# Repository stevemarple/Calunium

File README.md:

# Calunium

Calunium is an Arduino clone using the ATmega164A, ATmega164PA
ATmega324A, ATmega324PA, ATmega644A, ATmega644PA, ATmega1284 or
ATmega1284P microcontroller. The layout is designed for easy assembly
and maximum compatibility with the Arduino Uno, with additional
functionality being compatible with the Arduino Mega(2560).

## License

Unless indicated otherwise hardware is released under the Creative
Commons Attribution-ShareAlike 3.0 Unported (CC BY-SA 3.0)
http://creativecommons.org/licenses/by-sa/3.0/

Unless indicated otherwise software is released under the GNU Lesser
General Public License, version 2.1.
http://www.gnu.org/licenses/lgpl-2.1.html

## Versions

A brief description of the versions is given below. In each case
peripherals can be omitted form the build if not need.

### Stripboard version

The analogue pin mapping differs slightly for the stripboard
version. For more information see
http://blog.stevemarple.co.uk/2011/08/introducing-calunium-arduino-clone.html

### PCB version 1

Includes a real-time clock and LM61 temperature sensor. Standard
Arduino headers and JTAG, FTDI and auxillary power connectors. USB
connector for power and V-USB interface (not confirmed to work). Can
be operated at 3.3V or 5V depending upon build configuration. Not
jumper selectable. For more information see
http://blog.stevemarple.co.uk/2011/11/calunium-pcb-version.html.

### PCB version 2

Includes real-time clock, micro-SD socket, RFM12B radio module, and
LM61 temperature sensor. Arduino 1.0 headers with IOREF and dedicated
I2C pins. JTAG, FTDI and auxillary power connectors.  USB connector
for power only. Jumper-selectable 3.3V or 5V operation. For more
information see
http://blog.stevemarple.co.uk/2012/12/calunium-version-2.html

### PCB version 2.1

Includes MCP2200 USB-UART converter, real-time clock, micro-SD socket,
RFM12B radio module, and LM61 temperature sensor. Arduino 1.0 headers
with IOREF and dedicated I2C pins. JTAG and auxillary power
connectors. If the MCP2200 is fitted then the FTDI connector cannot be
fitted, but the USB socket is enabled for data. If the MCP2200 is not
fitted the FTDI connector can be, but the USB socket is for power
only. Jumper-selectable 3.3V or 5V operation. For more information see

The headers include
IOREF and dedicated I2C pins. For more information see
http://blog.stevemarple.co.uk/2013/02/calunium-version-21.html and
http://blog.stevemarple.co.uk/2012/12/calunium-version-2.html.

## Bootloader

Xboot and OptiBoot bootloaders are included. To avoid too many items
in boards menu the optiboot versions are commented out.

The xboot source files can be found at
https://github.com/stevemarple/xboot.

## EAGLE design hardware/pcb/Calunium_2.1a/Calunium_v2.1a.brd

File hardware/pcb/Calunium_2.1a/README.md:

# Calunium v2.1a PCB design

Calunium design files for Eagle 6.2.0.

Identical to Calunium v2.1 but corrects for silkscreen error on JP9.

## Licence
Creative Commons Attribution-ShareAlike 3.0 Unported (CC BY-SA 3.0)
http://creativecommons.org/licenses/by-sa/3.0/

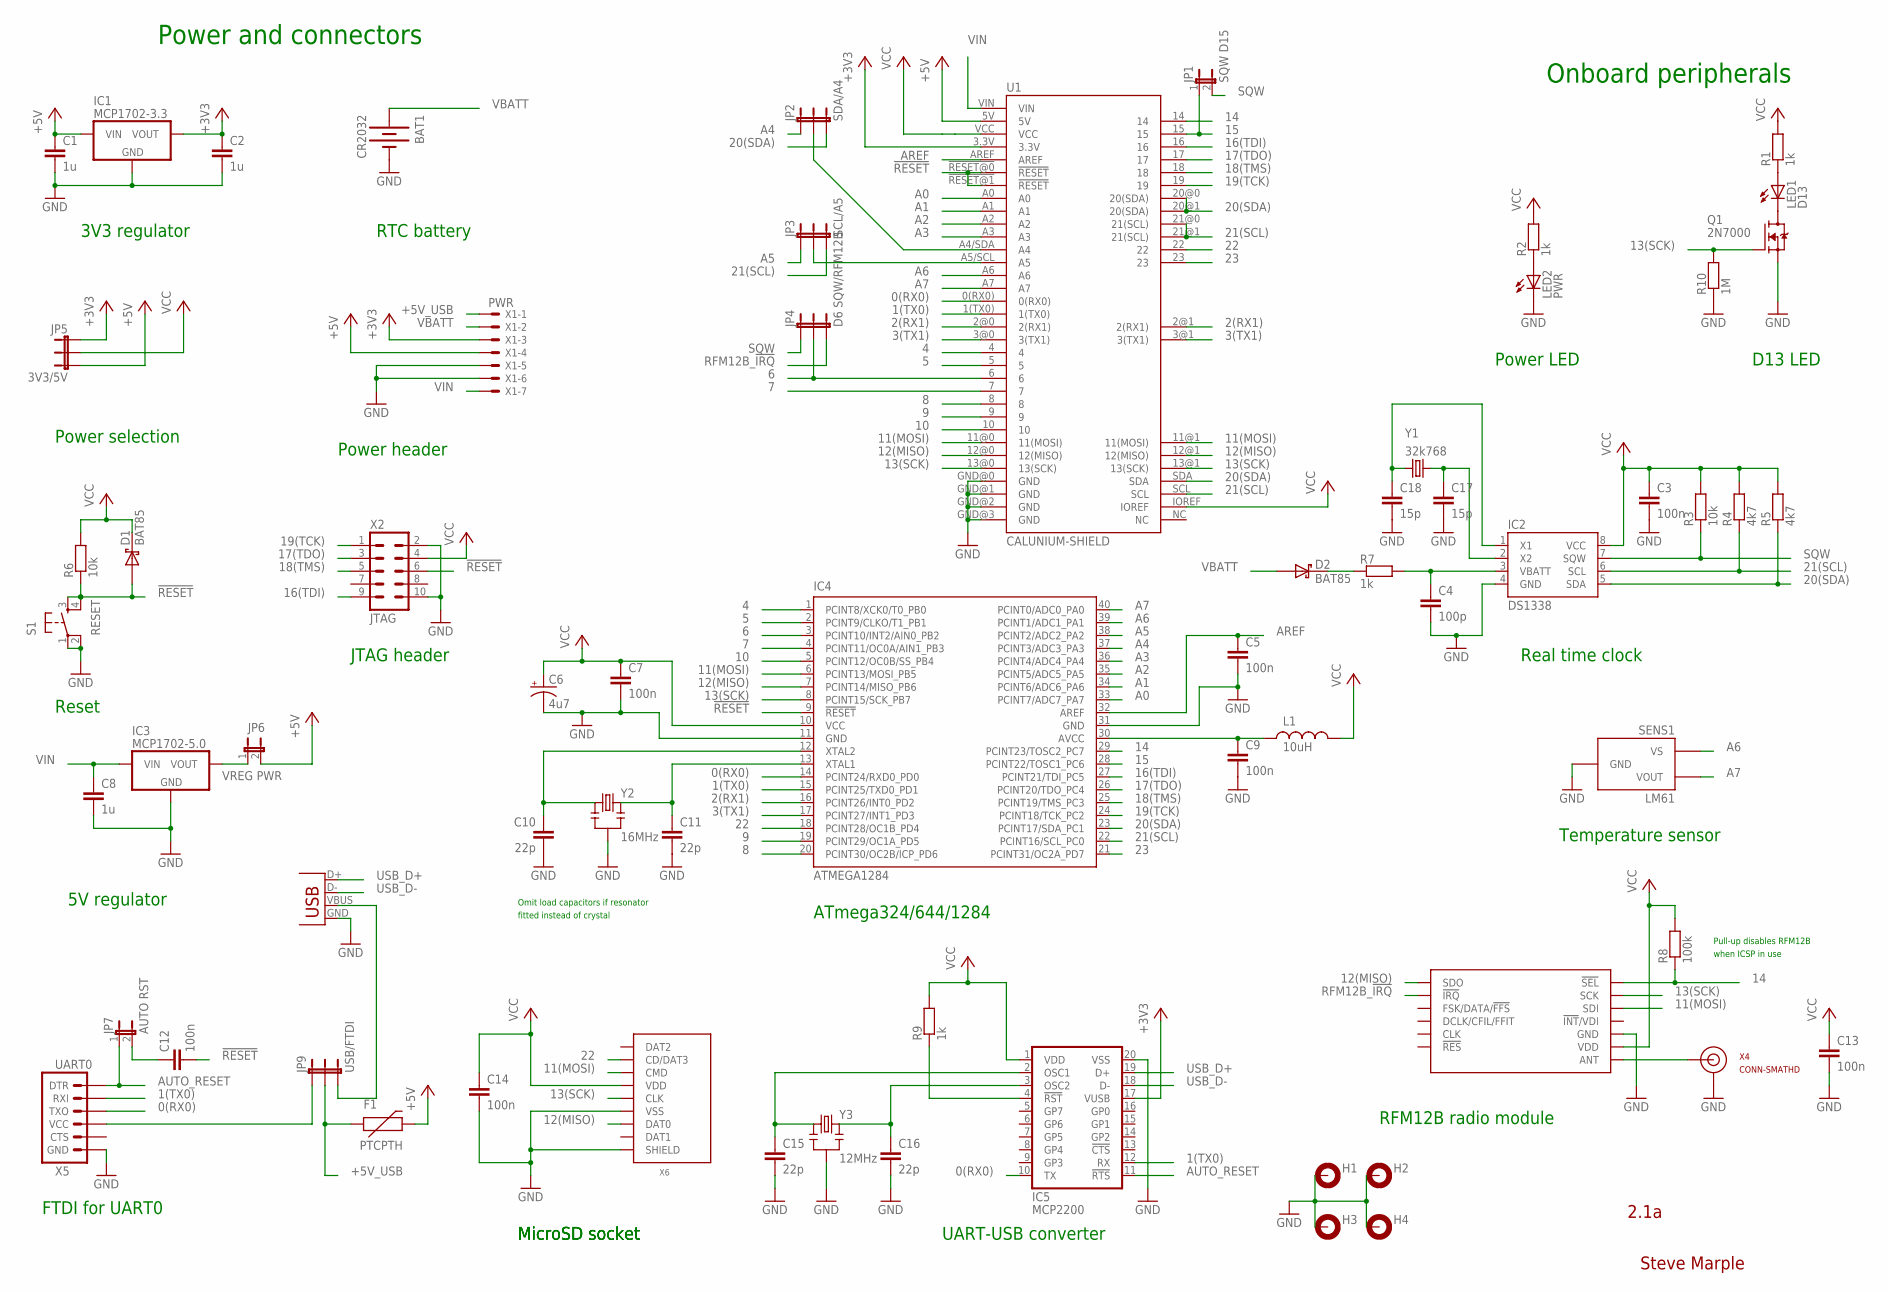
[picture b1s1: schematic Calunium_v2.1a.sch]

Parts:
BAT1: CR2032; BATTCOM_20MM_PTH
C1, C2, C8: 1u; CAP-PTH-5MM
C3, C5, C7, C9, C12, C13, C14: 100n; CAP-PTH-SMALL
C4: 100p; CAP-PTH-SMALL
C6: 4u7; CPOL-RADIAL-10UF-25V
C10, C11, C15, C16: 22p; CAP-PTH-SMALL
C17, C18: 15p; CAP-PTH-SMALL
D1, D2: BAT85; DIODE-TH-0.4
F1: PTCPTH; PTC
H1, H2, H3, H4: MOUNT-PAD-ROUND3.0; 3,0-PAD
IC1: MCP1702-3.3; TO-92
IC2: DS1338; SO08
IC3: MCP1702-5.0; TO-92
IC4: ATMEGA1284; DIL40
IC5: MCP2200; SO20
JP1: SQW D15; 1X02
JP2: SDA/A4; 1X03
JP3: SCL/A5; 1X03
JP4: D6 SQW/RFM12B; 1X03
JP5: 3V3/5V; 1X03
JP6: VREG PWR; 1X02
JP7: AUTO RST; 1X02
JP9: USB/FTDI; 1X03
L1: 10uH; RES-AXIAL-0.4
LED1: D13; LED3MM
LED2: PWR; LED3MM
Q1: 2N7000; TO-92
R1, R2, R7, R9: 1k; RES-AXIAL-0.4
R3, R6: 10k; RES-AXIAL-0.4
R4, R5: 4k7; RES-AXIAL-0.4
R8: 100k; RES-AXIAL-0.4
R10: 1M; RES-AXIAL-0.4
RF1: RFM12B
S1: RESET; TACTILE-PTH
SENS1: LM61; TO-92
U1: CALUNIUM-SHIELD; CALUNIUM-SHIELD-NO-OUTLINE-NO-HOLES-NO-TEXT-V2
X1: PWR; 22-23-2071
X2: JTAG; CON-HARTING-ML10
X3: USB; USB-B-PTH
X4: CONN-SMATHD; SMA-THD
X5: UART0; 1X06
X6: MICRO-SD-SOCKETHIROSE-DM3D; MICRO-SD-SOCKET-HIROSE-DM3D
Y1: 32k768; TC38H
Y2: 16MHz; HC49U-V-RESONATOR
Y3: 12MHz; HC49U-V-RESONATOR

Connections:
0(RX0): IC4.14 (PCINT24/RXD0_PD0), IC5.10 (TX), U1.0(RX0), X5.3 (TXO); also elsewhere on the board
1(TX0): IC4.15 (PCINT25/TXD0_PD1), IC5.12 (RX), U1.1(TX0), X5.2 (RXI); also elsewhere on the board
2(RX1): IC4.16 (PCINT26/INT0_PD2), U1.2@0 (2(RX1)), U1.2@1 (2(RX1)); also elsewhere on the board
3(TX1): IC4.17 (PCINT27/INT1_PD3), U1.3@0 (3(TX1)), U1.3@1 (3(TX1)); also elsewhere on the board
4: IC4.1 (PCINT8/XCK0/T0_PB0), U1.4; also elsewhere on the board
5: IC4.2 (PCINT9/CLKO/T1_PB1), U1.5; also elsewhere on the board
6: IC4.3 (PCINT10/INT2/AIN0_PB2), JP4.2, U1.6; also elsewhere on the board
7: IC4.4 (PCINT11/OC0A/AIN1_PB3), U1.7; also elsewhere on the board
8: IC4.20 (PCINT30/OC2B/ICP_PD6), U1.8; also elsewhere on the board
9: IC4.19 (PCINT29/OC1A_PD5), U1.9; also elsewhere on the board
10: IC4.5 (PCINT12/OC0B/SS_PB4), U1.10; also elsewhere on the board
11(MOSI): IC4.6 (PCINT13/MOSI_PB5), RF1.SDI, U1.11@0 (11(MOSI)), U1.11@1 (11(MOSI)), X6.CMD; also elsewhere on the board
12(MISO): IC4.7 (PCINT14/MISO_PB6), RF1.SDO, U1.12@0 (12(MISO)), U1.12@1 (12(MISO)), X6.DAT0; also elsewhere on the board
13(SCK): IC4.8 (PCINT15/SCK_PB7), Q1.2 (G), R10.P$2 (2), RF1.SCK, U1.13@0 (13(SCK)), U1.13@1 (13(SCK)), X6.CLK; also elsewhere on the board
14: IC4.29 (PCINT23/TOSC2_PC7), R8.P$1 (1), RF1.!SEL, U1.14; also elsewhere on the board
15: IC4.28 (PCINT22/TOSC1_PC6), JP1.1, U1.15; also elsewhere on the board
16(TDI): IC4.27 (PCINT21/TDI_PC5), U1.16, X2.9 (TDI); also elsewhere on the board
17(TDO): IC4.26 (PCINT20/TDO_PC4), U1.17, X2.3 (TDO); also elsewhere on the board
18(TMS): IC4.25 (PCINT19/TMS_PC3), U1.18, X2.5 (TMS); also elsewhere on the board
19(TCK): IC4.24 (PCINT18/TCK_PC2), U1.19, X2.1 (TCK); also elsewhere on the board
20(SDA): IC2.5 (SDA), IC4.23 (PCINT17/SDA_PC1), JP2.3, R5.P$1 (1), U1.20@0 (20(SDA)), U1.20@1 (20(SDA)), U1.SDA; also elsewhere on the board
21(SCL): IC2.6 (SCL), IC4.22 (PCINT16/SCL_PC0), JP3.3, R4.P$1 (1), U1.21@0 (21(SCL)), U1.21@1 (21(SCL)), U1.SCL; also elsewhere on the board
22: IC4.18 (PCINT28/OC1B_PD4), U1.22, X6.CD/DAT3; also elsewhere on the board
23: IC4.21 (PCINT31/OC2A_PD7), U1.23; also elsewhere on the board
!RESET: C12.2, D1.A, IC4.9 (!RESET), R6.P$1 (1), S1.3, S1.4, U1.!RESET@0 (!RESET), U1.!RESET@1 (!RESET), X2.6 (!SRST); also elsewhere on the board
+3V3: C2.1, IC1.3 (VOUT), IC5.17 (VUSB), JP5.1, U1.3.3V, X1.3; also elsewhere on the board
+5V: C1.1, F1.P$2 (2), IC1.2 (VIN), JP5.3, JP6.2, U1.5V, X1.4; also elsewhere on the board
+5V_USB: F1.P$1 (1), JP9.2, X1.1
A0: IC4.33 (PCINT7/ADC7_PA7), U1.A0; also elsewhere on the board
A1: IC4.34 (PCINT6/ADC6_PA6), U1.A1; also elsewhere on the board
A2: IC4.35 (PCINT5/ADC5_PA5), U1.A2; also elsewhere on the board
A3: IC4.36 (PCINT4/ADC4_PA4), U1.A3; also elsewhere on the board
A4: IC4.37 (PCINT3/ADC3_PA3), JP2.1
A4/SDA: JP2.2, U1.A4/SDA (A4); also elsewhere on the board
A5: IC4.38 (PCINT2/ADC2_PA2), JP3.1
A5/SCL: JP3.2, U1.A5/SCL (A5); also elsewhere on the board
A6: IC4.39 (PCINT1/ADC1_PA1), SENS1.1 (VS), U1.A6; also elsewhere on the board
A7: IC4.40 (PCINT0/ADC0_PA0), SENS1.2 (VOUT), U1.A7; also elsewhere on the board
AREF: C5.1, IC4.32 (AREF), U1.AREF; also elsewhere on the board
AUTO_RESET: IC5.11 (!RTS), JP7.1, X5.1 (DTR)
AVCC: C9.1, IC4.30 (AVCC), L1.P$1 (1)
GND: BAT1.2 (-), C1.2, C2.2, C3.2, C4.2, C5.2, C6.2 (-), C7.2, C8.2, C9.2, C10.2, C11.2, C13.2, C14.2, C15.2, C16.2, C17.2, C18.2, H1.B3,0, H2.B3,0, H3.B3,0, H4.B3,0, IC1.1 (GND), IC2.4 (GND), IC3.1 (GND), IC4.11 (GND), IC4.31 (GND), IC5.20 (VSS), LED2.K (C), Q1.1 (S), R10.P$1 (1), RF1.GND@0 (GND), RF1.GND@1 (GND), S1.1, S1.2, SENS1.3 (GND), U1.GND@0 (GND), U1.GND@1 (GND), U1.GND@2 (GND), U1.GND@3 (GND), X1.5, X1.6, X2.2 (GND), X2.10 (GND), X3.GND, X4.GND@0 (GND), X4.GND@1 (GND), X4.GND@2 (GND), X4.GND@3 (GND), X5.6 (GND), X6.GND (VSS), X6.SHIELD@0 (SHIELD), Y2.GND (2), Y3.GND (2); also elsewhere on the board
unnamed: C11.1, IC4.13 (XTAL1), Y2.2 (3)
unnamed: C10.1, IC4.12 (XTAL2), Y2.1
unnamed: LED1.A, R1.P$1 (1)
unnamed: LED1.K (C), Q1.3 (D)
unnamed: C18.1, IC2.1 (X1), Y1.2
unnamed: C16.1, IC5.3 (OSC2), Y3.2 (3)
unnamed: LED2.A, R2.P$1 (1)
unnamed: D2.C, R7.P$1 (1)
unnamed: JP9.1, X5.4 (VCC)
unnamed: C4.1, IC2.3 (VBATT), R7.P$2 (2)
unnamed: C17.1, IC2.2 (X2), Y1.1
unnamed: IC3.3 (VOUT), JP6.1
unnamed: C12.1, JP7.2
unnamed: JP9.3, X3.VBUS
unnamed: RF1.ANT, X4.SIG (SIGNAL)
unnamed: C15.1, IC5.2 (OSC1), Y3.1
unnamed: IC5.4 (!RST), R9.P$1 (1)
RFM12B_!IRQ: JP4.3, RF1.!IRQ
SQW: IC2.7 (SQW), JP1.2, JP4.1, R3.P$1 (1)
USB_D+: IC5.19 (D+), X3.D+
USB_D-: IC5.18 (D-), X3.D-
VBATT: BAT1.1 (+), D2.A, X1.2
VCC: C3.1, C6.1 (+), C7.1, C13.1, C14.1, D1.C, IC2.8 (VCC), IC4.10 (VCC), IC5.1 (VDD), JP5.2, L1.P$2 (2), R1.P$2 (2), R2.P$2 (2), R3.P$2 (2), R4.P$2 (2), R5.P$2 (2), R6.P$2 (2), R8.P$2 (2), R9.P$2 (2), RF1.VDD, U1.IOREF, U1.VCC, X2.4 (VTREF), X6.VDD; also elsewhere on the board
VIN: C8.1, IC3.2 (VIN), U1.VIN, X1.7; also elsewhere on the board

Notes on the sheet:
Power and connectors
Onboard peripherals
Real time clock
Temperature sensor
ATmega324/644/1284
FTDI for UART0
JTAG header
D13 LED
Reset
Power selection
Power header
3V3 regulator
RTC battery
Power LED
Steve Marple
2.1a
RFM12B radio module
5V regulator
Pull-up disables RFM12B
when ICSP in use
Omit load capacitors if resonator
fitted instead of crystal
MicroSD socket
UART-USB converter

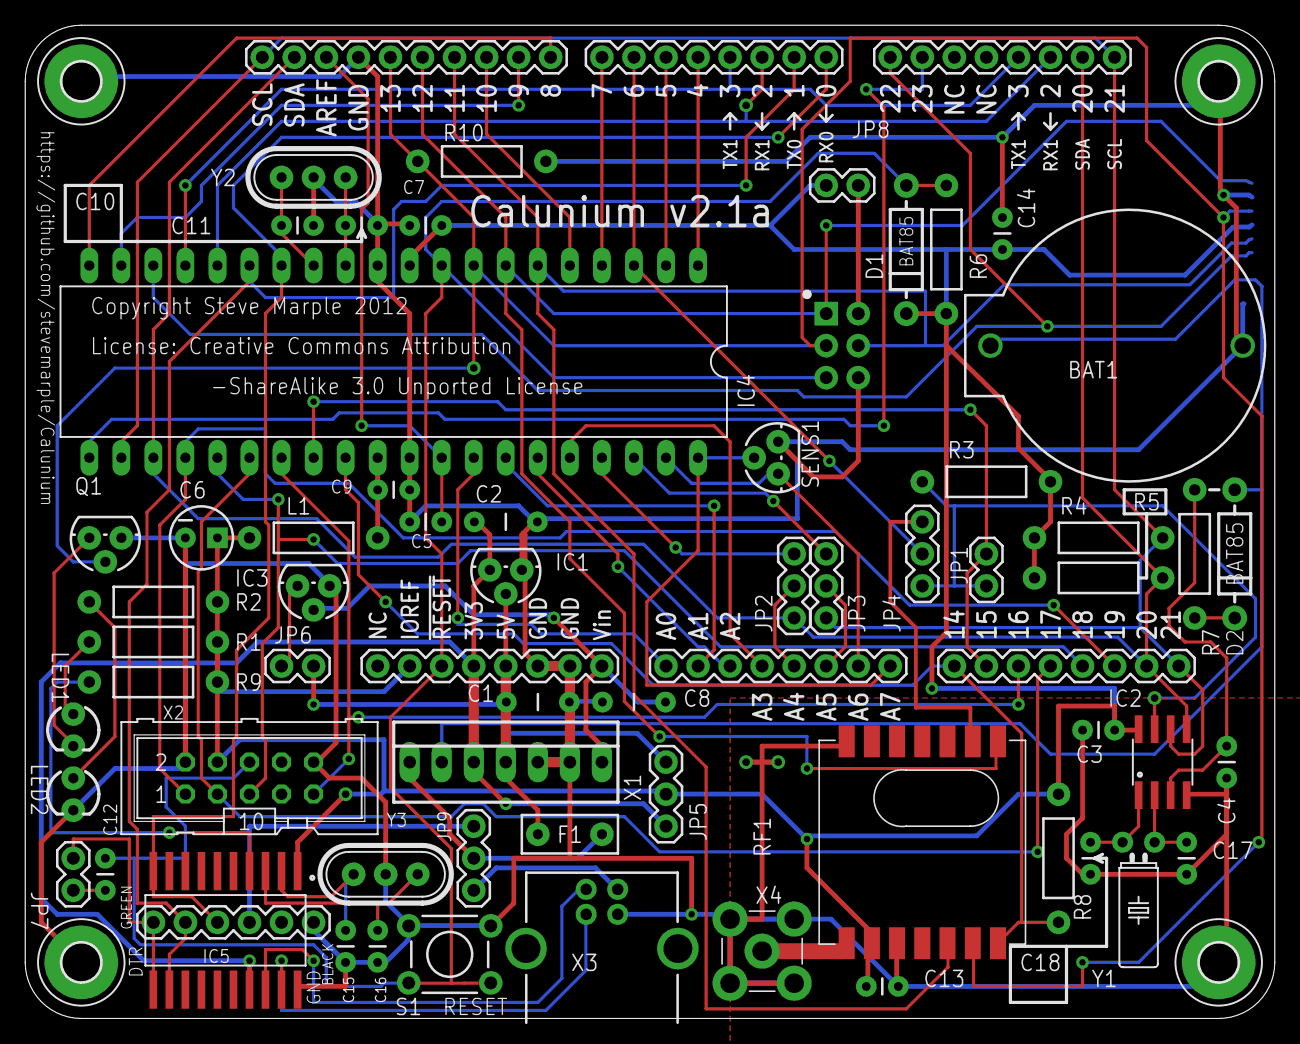
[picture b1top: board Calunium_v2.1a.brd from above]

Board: 2 copper layers, 99.1 x 78.7 mm, 67 parts (1 on the bottom side), 67 nets.

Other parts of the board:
JP8: ISP VCC; 1X02
U$1: CALUNIUM-SHIELD-V3V3-NO-HOLES-NO-TEXT; CALUNIUM-SHIELD-NO-OUTLINE-NO-HOLES-NO-TEXT-V3

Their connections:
0(RX0): U$1.0(RX0); also elsewhere on the board
1(TX0): U$1.1(TX0); also elsewhere on the board
2(RX1): U$1.2@0, U$1.2@1; also elsewhere on the board
3(TX1): U$1.3@0, U$1.3@1; also elsewhere on the board
4: U$1.4; also elsewhere on the board
5: U$1.5; also elsewhere on the board
6: U$1.6; also elsewhere on the board
7: U$1.7; also elsewhere on the board
8: U$1.8; also elsewhere on the board
9: U$1.9; also elsewhere on the board
10: U$1.10; also elsewhere on the board
11(MOSI): U$1.11@0, U$1.ISP_MOSI; also elsewhere on the board
12(MISO): U$1.12@0, U$1.ISP_MISO; also elsewhere on the board
13(SCK): U$1.13@0, U$1.ISP_SCK; also elsewhere on the board
14: U$1.14; also elsewhere on the board
15: U$1.15; also elsewhere on the board
16(TDI): U$1.16; also elsewhere on the board
17(TDO): U$1.17; also elsewhere on the board
18(TMS): U$1.18; also elsewhere on the board
19(TCK): U$1.19; also elsewhere on the board
20(SDA): U$1.20@0, U$1.20@1, U$1.SDA; also elsewhere on the board
21(SCL): U$1.21@0, U$1.21@1, U$1.SCL; also elsewhere on the board
22: U$1.22; also elsewhere on the board
23: U$1.23; also elsewhere on the board
!RESET: U$1.!ISP_RESET, U$1.!RESET@0; also elsewhere on the board
+3V3: U$1.3.3V; also elsewhere on the board
+5V: U$1.5V; also elsewhere on the board
A0: U$1.A0; also elsewhere on the board
A1: U$1.A1; also elsewhere on the board
A2: U$1.A2; also elsewhere on the board
A3: U$1.A3; also elsewhere on the board
A4/SDA: U$1.A4/SDA; also elsewhere on the board
A5/SCL: U$1.A5/SCL; also elsewhere on the board
A6: U$1.A6; also elsewhere on the board
A7: U$1.A7; also elsewhere on the board
AREF: U$1.AREF; also elsewhere on the board
GND: U$1.GND@0, U$1.GND@1, U$1.GND@2, U$1.GND@3; also elsewhere on the board
unnamed: JP8.1, U$1.ISP_VCC
VCC: JP8.2, U$1.IOREF; also elsewhere on the board
VIN: U$1.VIN; also elsewhere on the board

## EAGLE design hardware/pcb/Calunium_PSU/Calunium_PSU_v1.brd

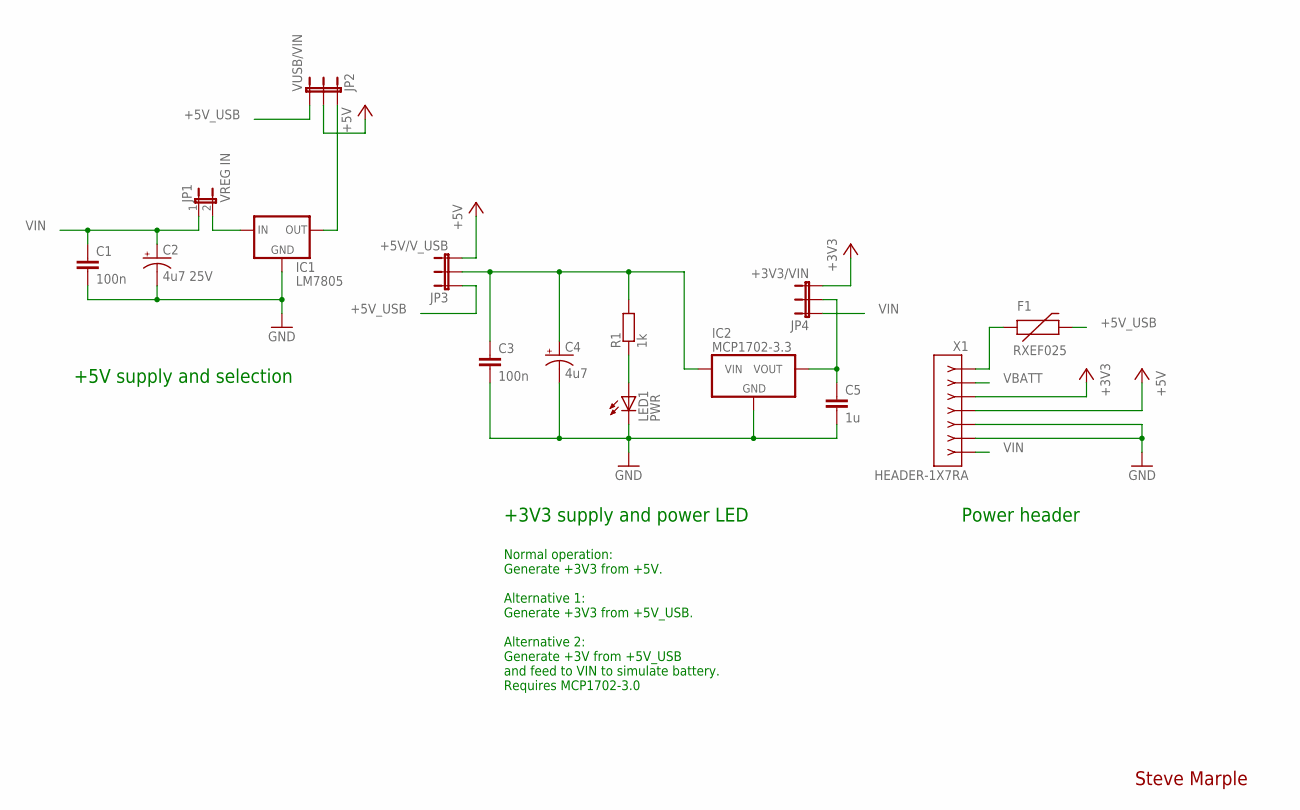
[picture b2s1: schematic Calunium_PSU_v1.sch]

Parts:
C1, C3: 100n; CAP-PTH-SMALL
C2: 4u7 25V; CPOL-RADIAL-10UF-25V
C4: 4u7; CPOL-RADIAL-10UF-25V
C5: 1u; CAP-PTH-5MM
F1: RXEF025; PTC
IC1: LM7805; 78XXL-NO-HOLE
IC2: MCP1702-3.3; TO-92
JP1: VREG IN; 1X02
JP2: VUSB/VIN; 1X03
JP3: +5V/V_USB; SJ_3
JP4: +3V3/VIN; SJ_3
LED1: PWR; LED3MM
R1: 1k; RES-AXIAL-0.4
X1: HEADER-1X7RA; HEADER-1X7-RA

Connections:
+3V3: JP4.3, X1.3
+5V: JP2.2, JP3.3, X1.4
+5V_USB: F1.P$2 (2), JP2.3, JP3.1
GND: C1.2, C2.2 (-), C3.2, C4.2 (-), C5.2, IC1.GND, IC2.1 (GND), LED1.K (C), X1.5, X1.6
unnamed: F1.P$1 (1), X1.1
unnamed: IC1.IN, JP1.2
unnamed: IC1.OUT, JP2.1
unnamed: C3.1, C4.1 (+), IC2.2 (VIN), JP3.2, R1.P$2 (2)
unnamed: C5.1, IC2.3 (VOUT), JP4.2
unnamed: LED1.A, R1.P$1 (1)
VBATT: X1.2
VIN: C1.1, C2.1 (+), JP1.1, JP4.1, X1.7

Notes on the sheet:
Power header
+5V supply and selection
Steve Marple
+3V3 supply and power LED
Normal operation: Generate +3V3 from +5V. Alternative 1: Generate +3V3 from +5V_USB. Alternative 2: Generate +3V from +5V_USB and feed to VIN to simulate battery. Requires MCP1702-3.0

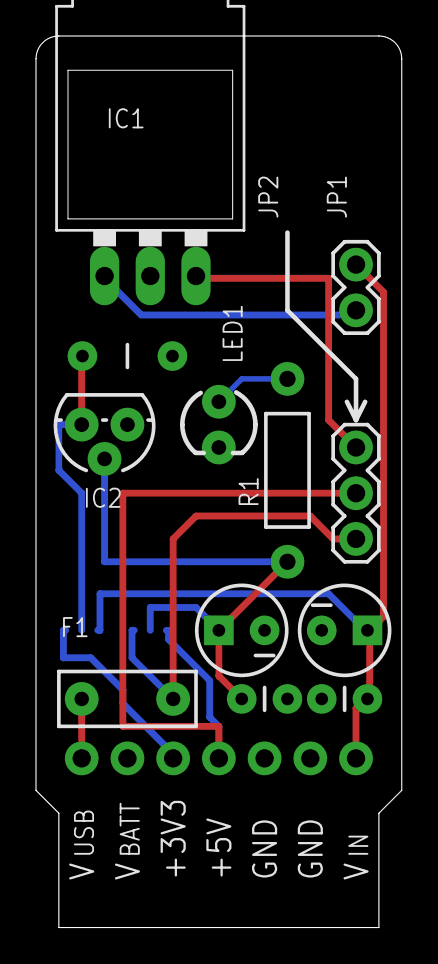
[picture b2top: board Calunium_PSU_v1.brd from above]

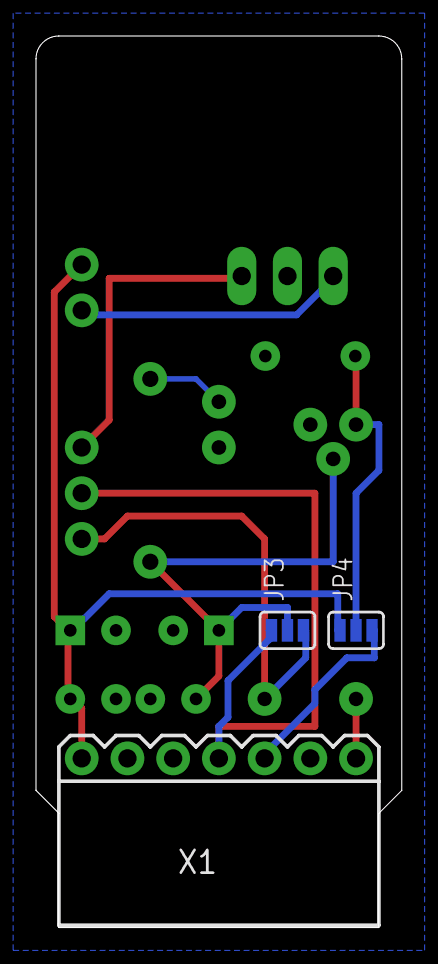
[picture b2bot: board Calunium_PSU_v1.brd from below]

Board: 2 copper layers, 20.3 x 49.5 mm, 15 parts (3 on the bottom side), 11 nets.

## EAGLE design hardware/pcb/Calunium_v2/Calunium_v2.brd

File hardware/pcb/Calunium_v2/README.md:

# Calunium v2.0 PCB design

Calunium design files for Eagle 6.2.0.

Proven design.

## Licence
Creative Commons Attribution-ShareAlike 3.0 Unported (CC BY-SA 3.0)
http://creativecommons.org/licenses/by-sa/3.0/

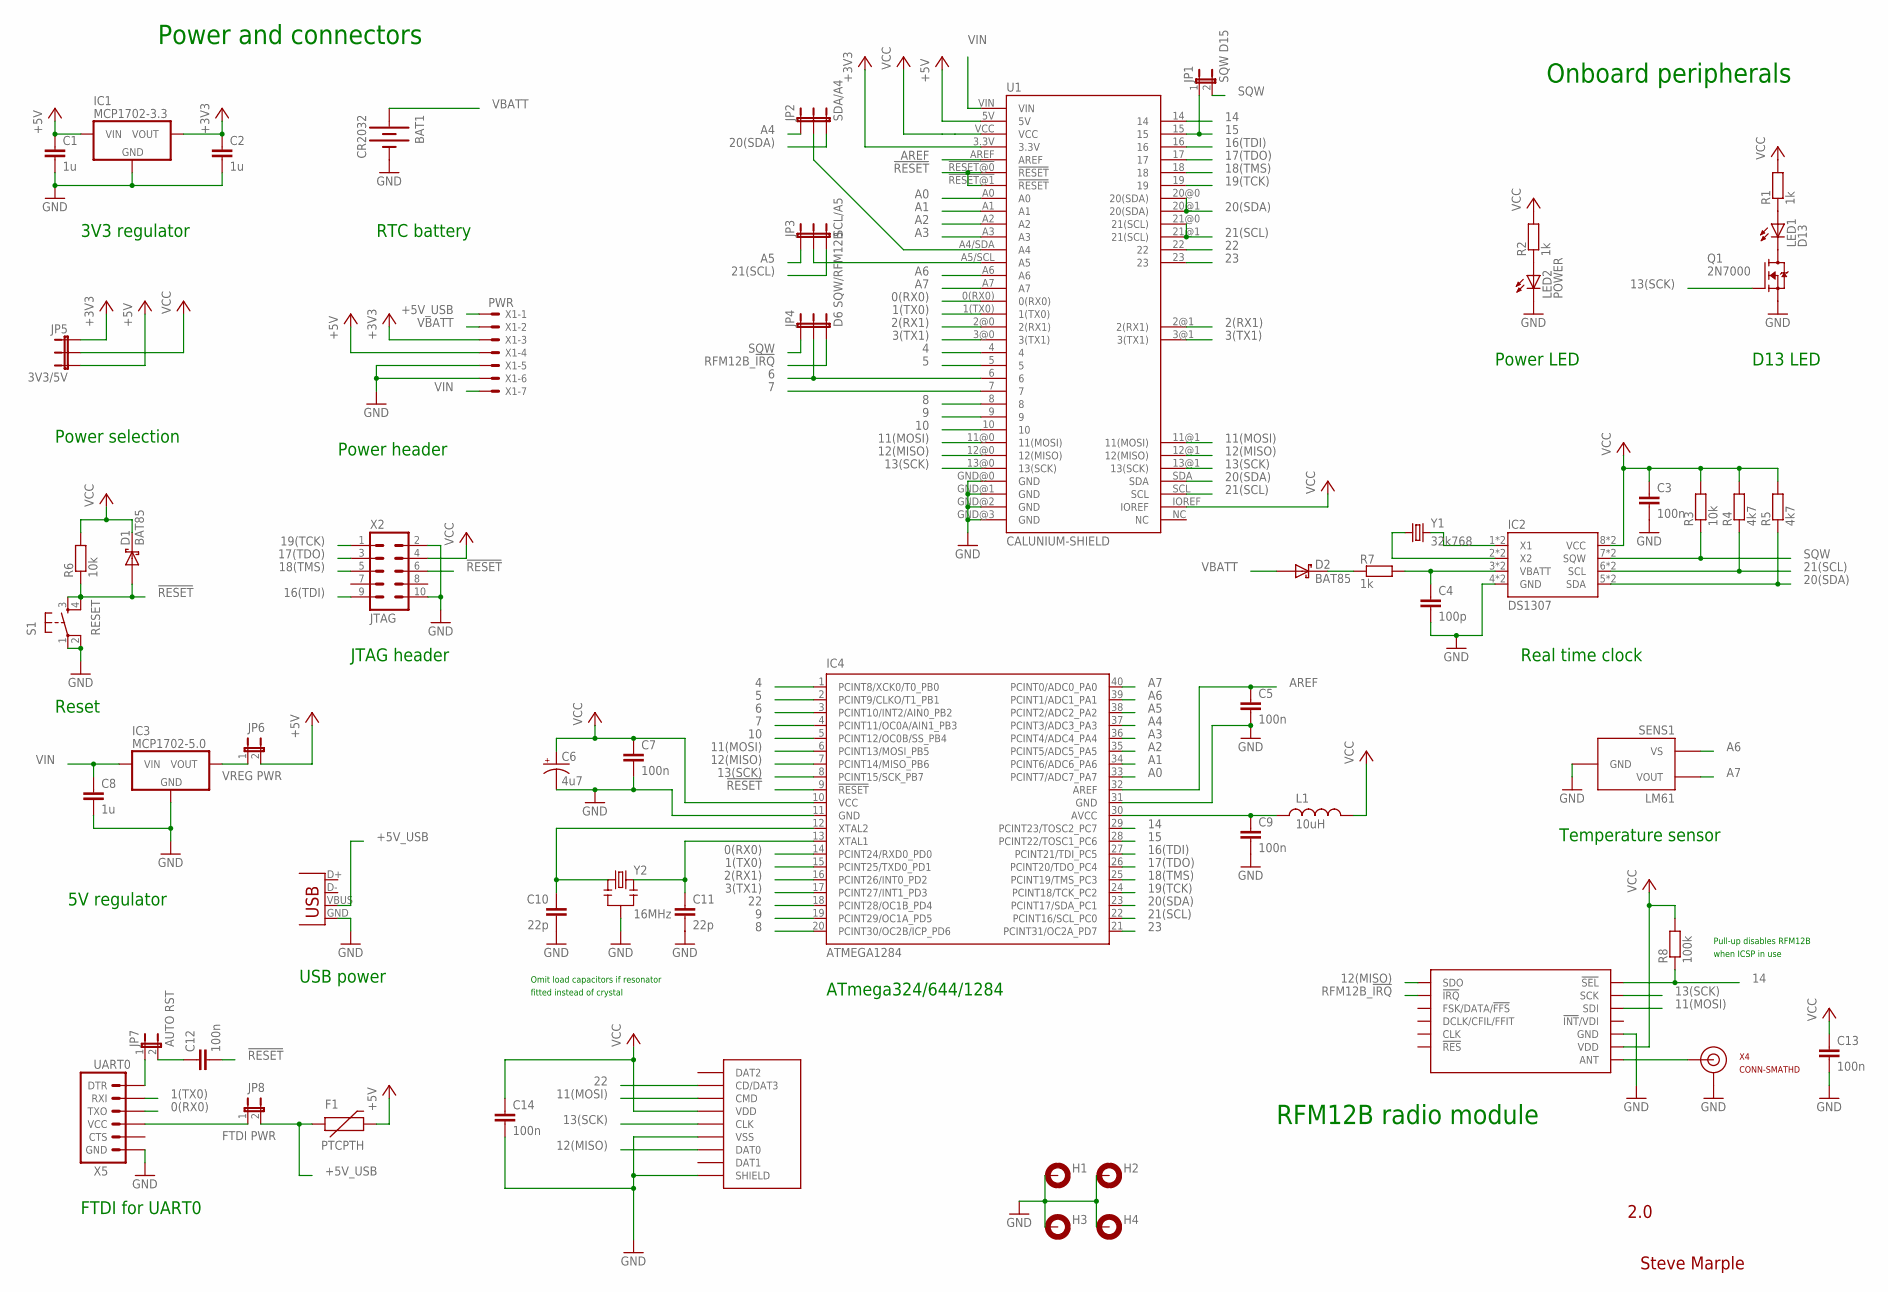
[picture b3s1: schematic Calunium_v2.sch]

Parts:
BAT1: CR2032; BATTCOM_20MM_PTH
C1, C2, C8: 1u; CAP-PTH-5MM
C3, C5, C7, C9, C12, C13, C14: 100n; CAP-PTH-SMALL
C4: 100p; CAP-PTH-SMALL
C6: 4u7; CPOL-RADIAL-10UF-25V
C10, C11: 22p; CAP-PTH-SMALL
D1, D2: BAT85; DIODE-TH-0.4
F1: PTCPTH; PTC
H1, H2, H3, H4: MOUNT-PAD-ROUND3.0; 3,0-PAD
IC1: MCP1702-3.3; TO-92
IC2: DS1307; DIL08-SOIC8
IC3: MCP1702-5.0; TO-92
IC4: ATMEGA1284; DIL40
JP1: SQW D15; 1X02
JP2: SDA/A4; 1X03
JP3: SCL/A5; 1X03
JP4: D6 SQW/RFM12B; 1X03
JP5: 3V3/5V; 1X03
JP6: VREG PWR; 1X02
JP7: AUTO RST; 1X02
JP8: FTDI PWR; 1X02
L1: 10uH; RES-AXIAL-0.4
LED1: D13; LED3MM
LED2: POWER; LED3MM
Q1: 2N7000; TO-92
R1, R2, R7: 1k; RES-AXIAL-0.4
R3, R6: 10k; RES-AXIAL-0.4
R4, R5: 4k7; RES-AXIAL-0.4
R8: 100k; RES-AXIAL-0.4
RF1: RFM12B
S1: RESET; TACTILE-PTH
SENS1: LM61; TO-92
U1: CALUNIUM-SHIELD; CALUNIUM-SHIELD-NO-OUTLINE-NO-HOLES-NO-TEXT-V2
U$1: MICRO-SD-SOCKETHIROSE-DM3D; MICRO-SD-SOCKET-HIROSE-DM3D
X1: PWR; 22-23-2071
X2: JTAG; CON-HARTING-ML10
X3: USB; USB-B-PTH
X4: CONN-SMATHD; SMA-THD
X5: UART0; MOLEX-1X6-RA_LOCK
Y1: 32k768; TC38H
Y2: 16MHz; HC49U-V-RESONATOR

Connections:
0(RX0): IC4.14 (PCINT24/RXD0_PD0), U1.0(RX0), X5.4 (TXO)
1(TX0): IC4.15 (PCINT25/TXD0_PD1), U1.1(TX0), X5.5 (RXI)
2(RX1): IC4.16 (PCINT26/INT0_PD2), U1.2@0 (2(RX1)), U1.2@1 (2(RX1))
3(TX1): IC4.17 (PCINT27/INT1_PD3), U1.3@0 (3(TX1)), U1.3@1 (3(TX1))
4: IC4.1 (PCINT8/XCK0/T0_PB0), U1.4
5: IC4.2 (PCINT9/CLKO/T1_PB1), U1.5
6: IC4.3 (PCINT10/INT2/AIN0_PB2), JP4.2, U1.6
7: IC4.4 (PCINT11/OC0A/AIN1_PB3), U1.7
8: IC4.20 (PCINT30/OC2B/ICP_PD6), U1.8
9: IC4.19 (PCINT29/OC1A_PD5), U1.9
10: IC4.5 (PCINT12/OC0B/SS_PB4), U1.10
11(MOSI): IC4.6 (PCINT13/MOSI_PB5), RF1.SDI, U1.11@0 (11(MOSI)), U1.11@1 (11(MOSI)), U$1.CMD
12(MISO): IC4.7 (PCINT14/MISO_PB6), RF1.SDO, U1.12@0 (12(MISO)), U1.12@1 (12(MISO)), U$1.DAT0
13(SCK): IC4.8 (PCINT15/SCK_PB7), Q1.2 (G), RF1.SCK, U1.13@0 (13(SCK)), U1.13@1 (13(SCK)), U$1.CLK
14: IC4.29 (PCINT23/TOSC2_PC7), R8.P$1 (1), RF1.!SEL, U1.14
15: IC4.28 (PCINT22/TOSC1_PC6), JP1.1, U1.15
16(TDI): IC4.27 (PCINT21/TDI_PC5), U1.16, X2.9 (TDI)
17(TDO): IC4.26 (PCINT20/TDO_PC4), U1.17, X2.3 (TDO)
18(TMS): IC4.25 (PCINT19/TMS_PC3), U1.18, X2.5 (TMS)
19(TCK): IC4.24 (PCINT18/TCK_PC2), U1.19, X2.1 (TCK)
20(SDA): IC2.5 (SDA), IC2.5@1 (SDA), IC4.23 (PCINT17/SDA_PC1), JP2.3, R5.P$1 (1), U1.20@0 (20(SDA)), U1.20@1 (20(SDA)), U1.SDA
21(SCL): IC2.6 (SCL), IC2.6@1 (SCL), IC4.22 (PCINT16/SCL_PC0), JP3.3, R4.P$1 (1), U1.21@0 (21(SCL)), U1.21@1 (21(SCL)), U1.SCL
22: IC4.18 (PCINT28/OC1B_PD4), U1.22, U$1.CD/DAT3
23: IC4.21 (PCINT31/OC2A_PD7), U1.23
!RESET: C12.2, D1.A, IC4.9 (!RESET), R6.P$1 (1), S1.3, S1.4, U1.!RESET@0 (!RESET), U1.!RESET@1 (!RESET), X2.6 (!SRST)
+3V3: C2.1, IC1.3 (VOUT), JP5.1, U1.3.3V, X1.3
+5V: C1.1, F1.P$2 (2), IC1.2 (VIN), JP5.3, JP6.2, U1.5V, X1.4
+5V_USB: F1.P$1 (1), JP8.2, X1.1, X3.VBUS
A0: IC4.33 (PCINT7/ADC7_PA7), U1.A0
A1: IC4.34 (PCINT6/ADC6_PA6), U1.A1
A2: IC4.35 (PCINT5/ADC5_PA5), U1.A2
A3: IC4.36 (PCINT4/ADC4_PA4), U1.A3
A4: IC4.37 (PCINT3/ADC3_PA3), JP2.1
A5: IC4.38 (PCINT2/ADC2_PA2), JP3.1
A6: IC4.39 (PCINT1/ADC1_PA1), SENS1.1 (VS), U1.A6
A7: IC4.40 (PCINT0/ADC0_PA0), SENS1.2 (VOUT), U1.A7
AREF: C5.1, IC4.32 (AREF), U1.AREF
AVCC: C9.1, IC4.30 (AVCC), L1.P$1 (1)
GND: BAT1.2 (-), C1.2, C2.2, C3.2, C4.2, C5.2, C6.2 (-), C7.2, C8.2, C9.2, C10.2, C11.2, C13.2, C14.2, H1.B3,0, H2.B3,0, H3.B3,0, H4.B3,0, IC1.1 (GND), IC2.4 (GND), IC2.4@1 (GND), IC3.1 (GND), IC4.11 (GND), IC4.31 (GND), LED2.K (C), Q1.1 (S), RF1.GND@0 (GND), RF1.GND@1 (GND), S1.1, S1.2, SENS1.3 (GND), U1.GND@0 (GND), U1.GND@1 (GND), U1.GND@2 (GND), U1.GND@3 (GND), U$1.GND (VSS), U$1.SHIELD@0 (SHIELD), X1.5, X1.6, X2.2 (GND), X2.10 (GND), X3.GND, X4.GND@0 (GND), X4.GND@1 (GND), X4.GND@2 (GND), X4.GND@3 (GND), X5.1 (GND), Y2.GND (2)
unnamed: C11.1, IC4.13 (XTAL1), Y2.2 (3)
unnamed: C10.1, IC4.12 (XTAL2), Y2.1
unnamed: LED1.A, R1.P$1 (1)
unnamed: LED1.K (C), Q1.3 (D)
unnamed: IC2.1 (X1), IC2.1@1 (X1), Y1.2
unnamed: JP2.2, U1.A4/SDA (A4)
unnamed: LED2.A, R2.P$1 (1)
unnamed: D2.C, R7.P$1 (1)
unnamed: JP8.1, X5.3 (VCC)
unnamed: C4.1, IC2.3 (VBATT), IC2.3@1 (VBATT), R7.P$2 (2)
unnamed: IC2.2 (X2), IC2.2@1 (X2), Y1.1
unnamed: JP3.2, U1.A5/SCL (A5)
unnamed: IC3.3 (VOUT), JP6.1
unnamed: JP7.1, X5.6 (DTR)
unnamed: C12.1, JP7.2
unnamed: RF1.ANT, X4.SIG (SIGNAL)
RFM12B_!IRQ: JP4.3, RF1.!IRQ
SQW: IC2.7 (SQW), IC2.7@1 (SQW), JP1.2, JP4.1, R3.P$1 (1)
VBATT: BAT1.1 (+), D2.A, X1.2
VCC: C3.1, C6.1 (+), C7.1, C13.1, C14.1, D1.C, IC2.8 (VCC), IC2.8@1 (VCC), IC4.10 (VCC), JP5.2, L1.P$2 (2), R1.P$2 (2), R2.P$2 (2), R3.P$2 (2), R4.P$2 (2), R5.P$2 (2), R6.P$2 (2), R8.P$2 (2), RF1.VDD, U1.IOREF, U1.VCC, U$1.VDD, X2.4 (VTREF)
VIN: C8.1, IC3.2 (VIN), U1.VIN, X1.7

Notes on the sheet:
Power and connectors
Onboard peripherals
Real time clock
Temperature sensor
ATmega324/644/1284
USB power
FTDI for UART0
JTAG header
D13 LED
Reset
Power selection
Power header
3V3 regulator
RTC battery
Power LED
Steve Marple
2.0
RFM12B radio module
5V regulator
Pull-up disables RFM12B
when ICSP in use
Omit load capacitors if resonator
fitted instead of crystal

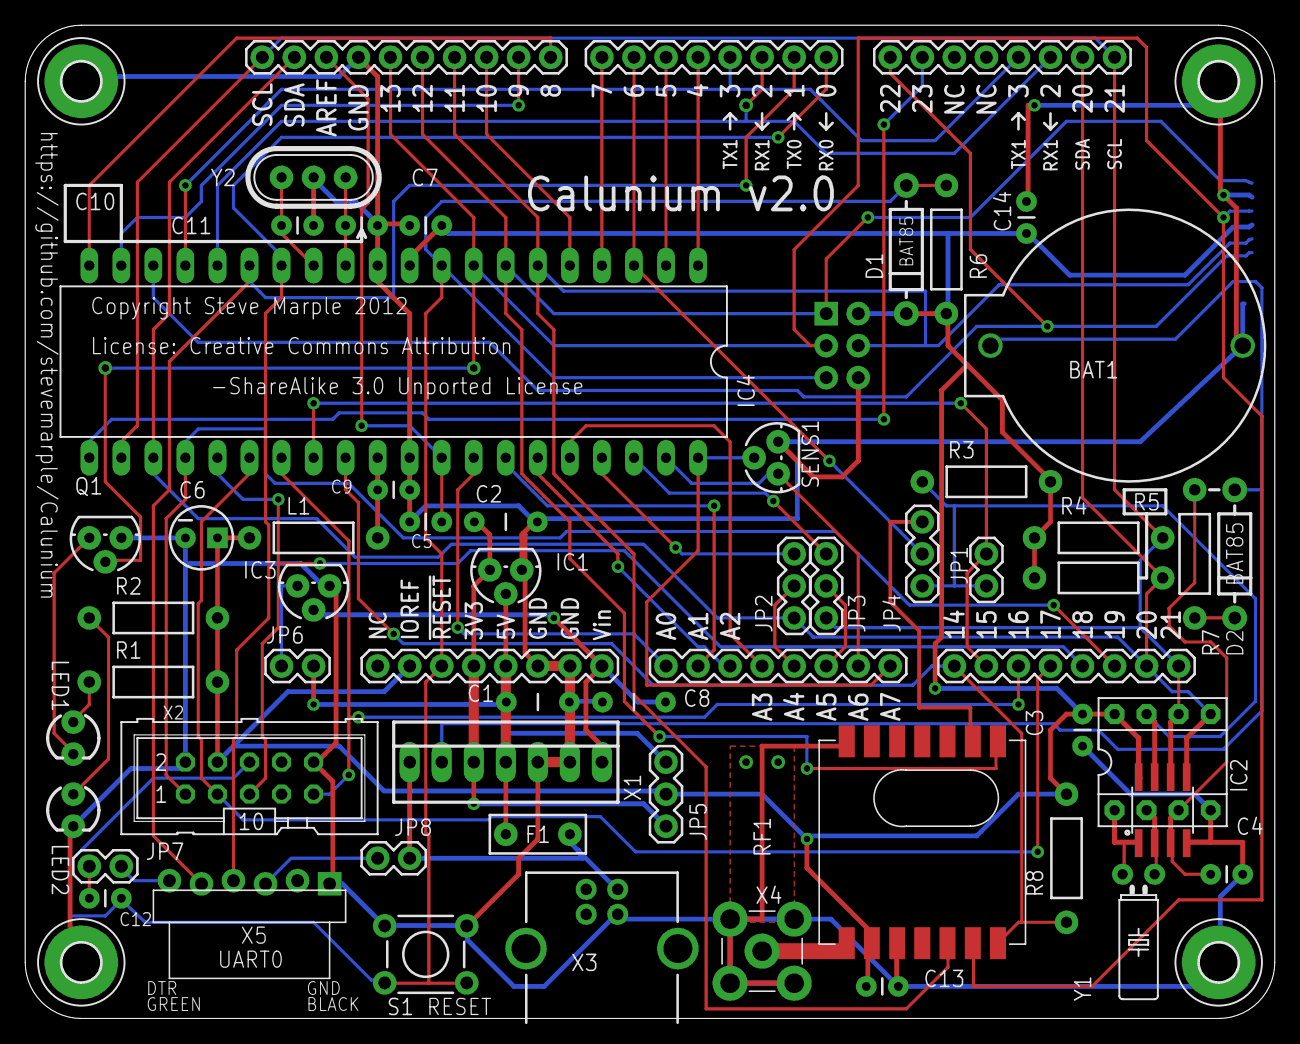
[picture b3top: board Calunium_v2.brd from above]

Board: 2 copper layers, 99.1 x 78.7 mm, 58 parts (1 on the bottom side), 60 nets.

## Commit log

2011-08-16 Initial commit.
2011-08-23 Updated readme to include URLs to construction pages and photographs.
2011-10-10 Moved stripboard deisgns to separate directory.
2011-10-10 Added Eagle PCB design files.
    Added Eagle schematic (.sch) and board (.brd) files, the schematic
    exported in PDF and PNG formats, and the Gerber RS-274x format files
    (.{G[TB][LOS],TXT}) used for PCB manufacture.
2011-10-10 Updated readme.txt now that strip board and PCB designs exist.
2011-11-19 Adding files to support Calunium in the Arduino IDE.
2011-11-19 Adding pin change details.
2011-11-19 Updating the project description.
2011-12-11 Adding bootloader files.
2011-12-11 Fixing bootloader names in boards.txt.
2011-12-11 Removing old bootloader files.
2011-12-25 Adding link to information about the PCB version.
2012-01-11 Indicating Arduino 1.0 is required.
2012-01-14 Updating core files from Arduino master respoitory to support interrupts
2012-01-14 Adding examples for using the on-board real time clock
2012-01-15 Adding example to use the RTC with timer/counter input
2012-01-16 Adding example to use the RTC with pin change interrupts.
2012-01-17 Clean up example.
2012-01-20 Adding readme file for the examples.
2012-01-22 Fixing the definition (pcb) of CALUNIUM_VARIANT to match the path.
2012-01-22 Adding CALUNIUM and CALUNIUM_VARIANT #defines.
2012-01-26 Adding/updating RTC examples.
2012-02-19 Adding entries for Optiboot bootloader versions.
2012-04-30 Adding optiboot files.
2012-04-30 Using wiring_analog.c from mighty-1284p to support correct analog mapping.
2012-04-30 Fixing pin mapping to use the features from mighty-1284p.
2012-04-30 Restoring the CALUNIUM and CALUNIUM_VARIANT #defines
2012-05-01 Ensuring C linkage for pin mapping header files
2012-06-18 Preliminary Calunium v2 PCB design
2012-06-18 Moving v1 schematics.
2012-06-18 Update master
2012-06-18 Update Calunium_v2 README
2012-09-04 Updating v2.0 PCB design files.
2012-09-18 Adding example to show disabling JTAG in software.
2012-12-01 Fixing C compatibility. LED pin renamed to LED_BUILTIN.
2012-12-01 Adding extra board options for xboot.
2012-12-22 Adding description of Calunium v1 status.
2012-12-22 Add entry for 16MHz xboot bootloader version.
2013-01-09 Indicate that Calunium v2 design is known to be good.
2013-01-09 Adding Calunium v2.1 design files.
    Almost identical to v2.1 but with MCP2200 USB interface added. Untested layout.
2013-01-10 Add load capacitors for MCP7941x RTC. Removed DIP footprint for RTC.
2013-02-08 Fix for SoftwareSerial compilation. (Kenneth Fuglsang Christensen)
2013-02-09 Fix for SoftwareSerial compilation. (Kenneth Fuglsang Christensen).
2013-02-10 Adding xboot hex files for standard crystal freqs, and RC oscillator.
2013-02-10 Use standard arduino core. Reduced baudrate for 8MHz board.
2013-02-11 Updated project information.
2013-02-11 Reverting back to using own core. Need analogInputToDigitalPin().
2013-02-19 Adding correction for silkscreen error.
2013-03-23 Fixing to compile with gcc v4.7.2.
2014-01-18 Fixing error where MCP2200 autoreset was not routed through JP7.
2014-01-23 Adding Eagle PCB design for PSU which plugs onto Molex power connector.
2014-01-29 Adding 1M pull-down resistor on D13.
2014-01-31 Adding juumper to disconnect VCC from ISP header, routing improvements.
2014-03-05 Ignoring Eagle backup files and unwanted Gerber files.
2014-05-16 Adding example demonstrating analogRead() and analogReference().
2014-11-07 Minor routing changes to increase trace separation.
2014-11-07 Adding design rules file used for PCB layout.
2014-11-07 Renamed directory to follow pattern used previously for different versions.
2014-12-05 Adding .gitignore for Eagle files.
2015-10-07 Refactor to support arduino v1.0 and v1.6
2015-10-07 Update board definitions
2015-10-07 Add Eagle library
2015-10-12 Fix speed menu entries.
2015-10-13 Updated and new xboot bootloaders.
    Compiled with avr-gcc version 4.8.1. New bootloaders for
    ATmega1284 (non-P version). Watchdog timer enabled (8s).
2015-12-13 Add missing bootloader tool entries
2015-12-13 Fix PCB/stripboard variant menu option
2015-12-13 Add menu option to include a custom file for all compilation units
2015-12-15 Add digitalPinToInterrupt macro
2016-01-12 Use MHz values for clock speeds in menu choices
2018-06-13 Add Dragon JTAG with -F option
    For convenience with programming ATmega1284 (non-P) as ATmega1284P.
2019-03-21 Add home page for Github pages
    Redirect to Calunium repository.

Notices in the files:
hardware/pcb/Calunium_2.1a/Calunium_v2.1a.brd:
License: Creative Commons Attribution
Copyright Steve Marple 2012
